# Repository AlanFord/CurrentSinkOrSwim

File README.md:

# CurrentSinkOrSwim
Building a current sink for battery testing in Contextual Electronics.

Here's the project so far:

and

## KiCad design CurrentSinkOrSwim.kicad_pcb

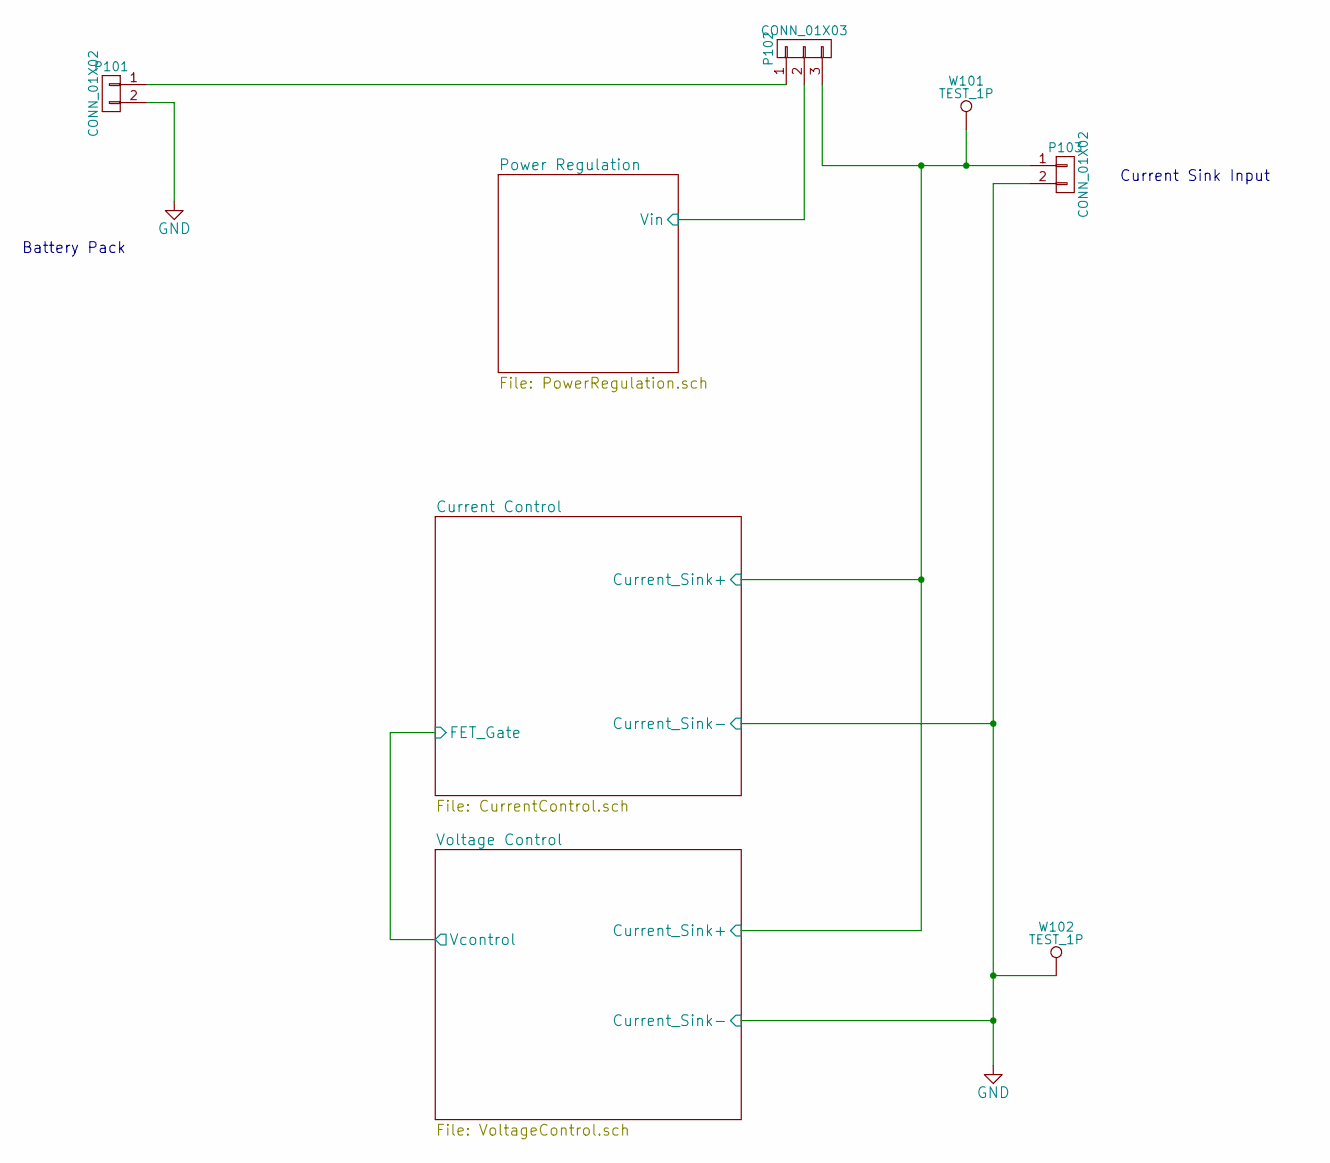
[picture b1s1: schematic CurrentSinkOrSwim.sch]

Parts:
P101, P103: CONN_01X02; Terminal_Block_200_mil; MPN OSTTC022162
P102: CONN_01X03; Pin_Header_Straight_1x03
W101, W102: TEST_1P; Measurement_Point_Round-SMD-Pad_Small

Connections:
/Current Control/Current_Sink+: P102.3, P103.1, W101.1; also elsewhere on the board
/Power Regulation/Vin: P102.2; also elsewhere on the board
GND: P101.2, P103.2, W102.1; also elsewhere on the board
unnamed: P101.1, P102.1

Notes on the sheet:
Battery Pack
Current Sink Input

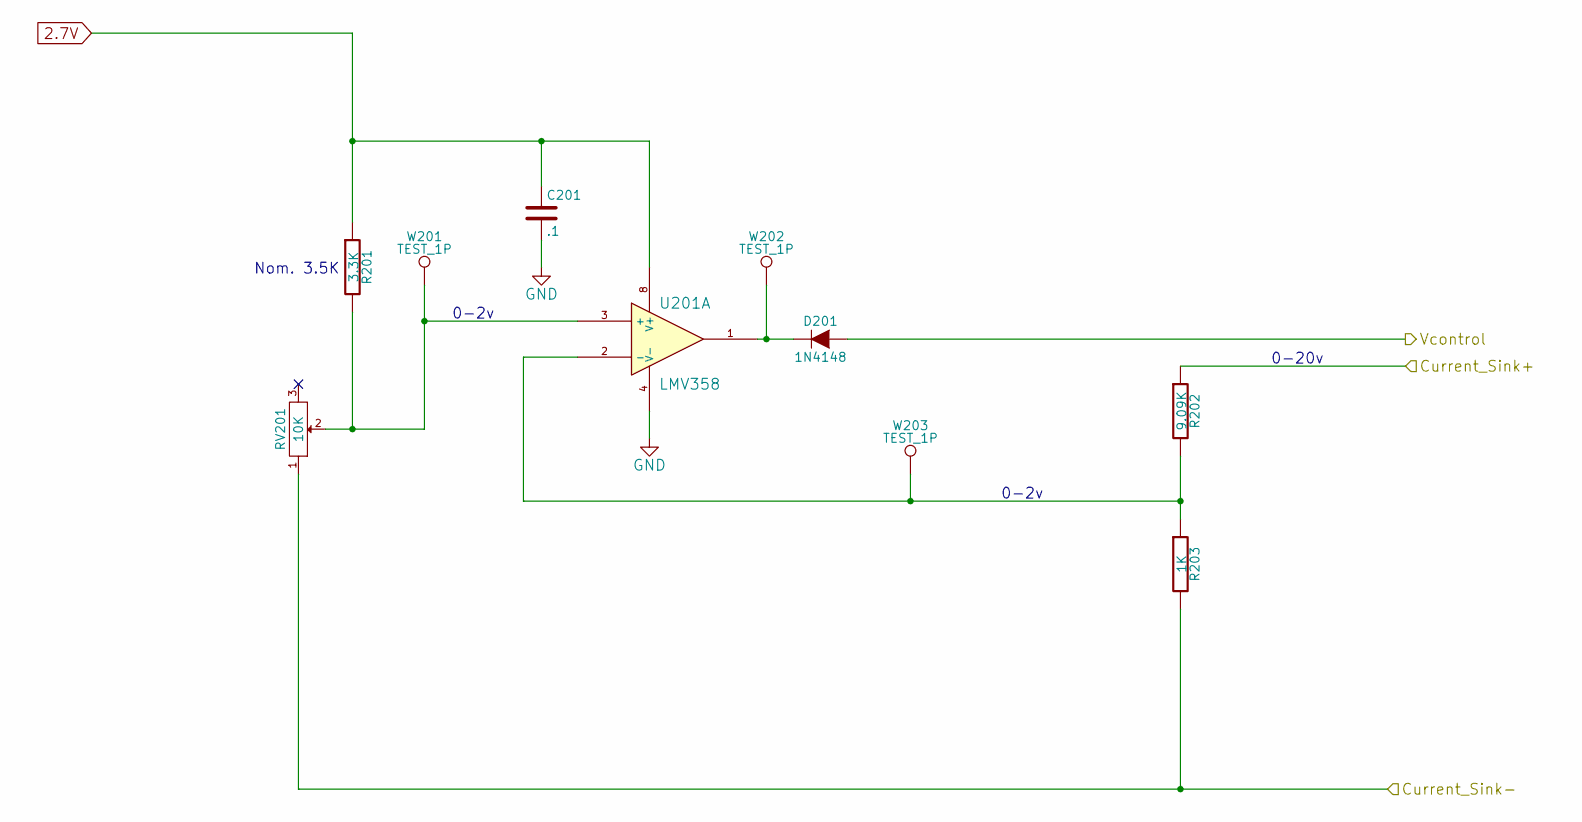
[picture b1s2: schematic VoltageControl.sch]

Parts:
C201: .1; C_0805
D201: 1N4148; SOD-323; MPN 1N4148WS-7-F
R201: 3.3K; R_0805
R202: 9.09K; R_0805
R203: 1K; R_0805
RV201: 10K; P090L-02F25BR10K; MPN P090L-02F25BR10K
U201: LMV358; SOIC-8-N; MPN LMV358IDT
W201, W202, W203: TEST_1P; Measurement_Point_Round-SMD-Pad_Small

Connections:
2.7V: C201.1, R201.1, U201.8 (V+); also elsewhere on the board
/Current Control/Current_Sink+: R202.1; also elsewhere on the board
/Current Control/FET_Gate: D201.2 (A); also elsewhere on the board
GND: C201.2, R203.2, RV201.1, U201.4 (V-); also elsewhere on the board
unnamed: D201.1 (K), U201.1, W202.1
unnamed: R201.2, RV201.2, U201.3 (+), W201.1
unnamed: R202.2, R203.1, U201.2 (-), W203.1

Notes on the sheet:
0-2v
0-20v
Nom. 3.5K

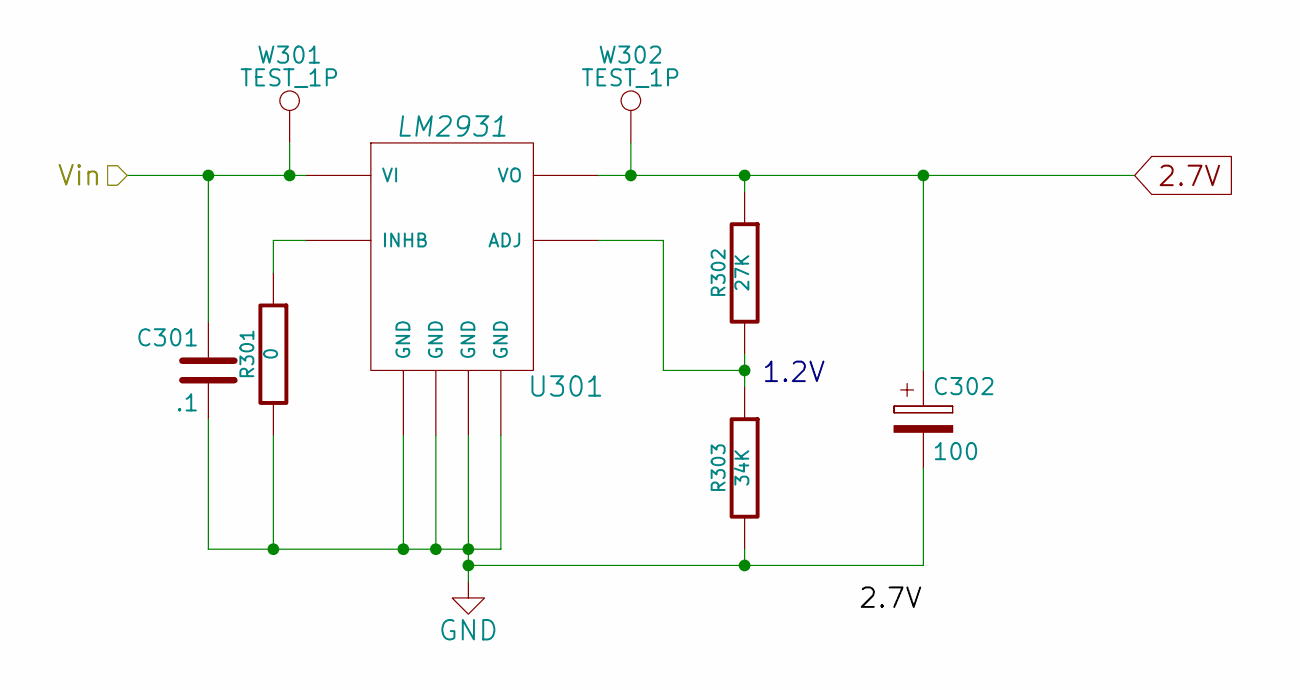
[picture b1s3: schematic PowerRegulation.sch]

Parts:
C301: .1; C_0805
C302: 100; PCE3867CT-ND; MPN PCE3867CT-ND
R301: 0; R_0805; MPN Value
R302: 27K; R_0805; MPN Value
R303: 34K; R_0805
U301: LM2931; SOIC-8-N; MPN LM2931D-R
W301, W302: TEST_1P; Measurement_Point_Round-SMD-Pad_Small

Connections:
2.7V: C302.1, R302.1, U301.1 (VO), W302.1; also elsewhere on the board
/Power Regulation/Vin: C301.1, U301.8 (VI), W301.1; also elsewhere on the board
GND: C301.2, C302.2, R301.2, R303.2, U301.2 (GND), U301.3 (GND), U301.6 (GND), U301.7 (GND); also elsewhere on the board
unnamed: R301.1, U301.5 (INHB)
unnamed: R302.2, R303.1, U301.4 (ADJ)

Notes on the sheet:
1.2V

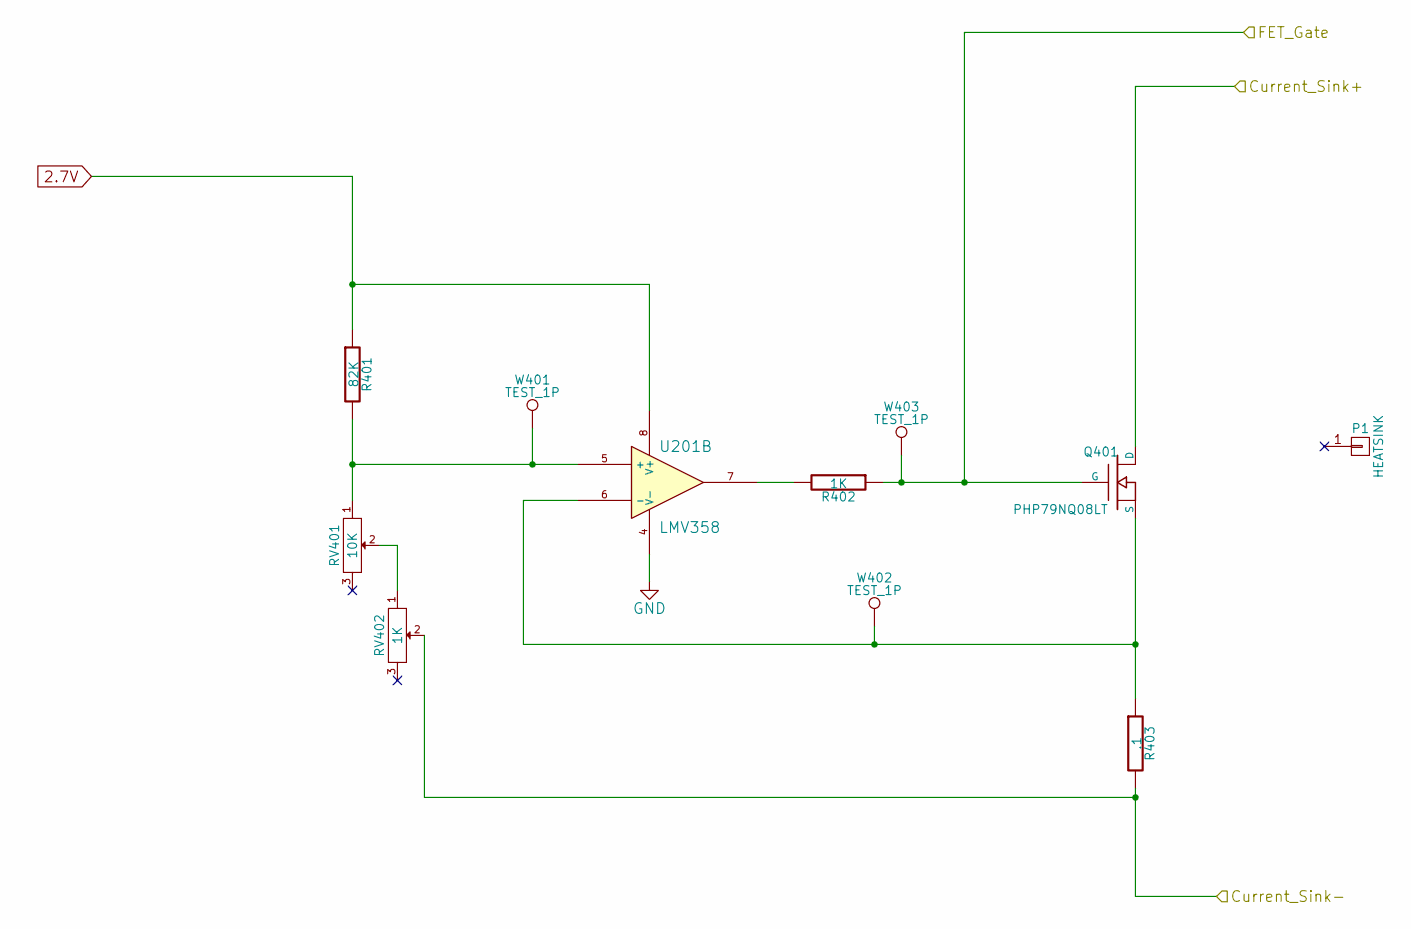
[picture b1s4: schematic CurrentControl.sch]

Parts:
P1: HEATSINK; FA-T220-38E; MPN FA-T220-38E
Q401: PHP79NQ08LT; TO-220_FET-GDS_Vertical; MPN PHP79NQ08LT,127
R401: 82K; R_0805
R402: 1K; R_0805
R403: .1; R_2512; MPN CRA2512-FZ-R100ELF
RV401: 10K; P090L-02F25BR10K; MPN P090L-02F25BR10K
RV402: 1K; MPN P110KV1-1F25BR1K
U201: LMV358; SOIC-8-N
W401, W402, W403: TEST_1P; Measurement_Point_Round-SMD-Pad_Small

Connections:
2.7V: R401.1, U201.8 (V+); also elsewhere on the board
/Current Control/Current_Sink+: Q401.D; also elsewhere on the board
/Current Control/FET_Gate: Q401.G, R402.1, W403.1; also elsewhere on the board
GND: R403.2, RV401.2, RV402.1, RV402.2, U201.4 (V-); also elsewhere on the board
unnamed: Q401.S, R403.1, U201.6 (-), W402.1
unnamed: R401.2, RV401.1, U201.5 (+), W401.1
unnamed: R402.2, U201.7

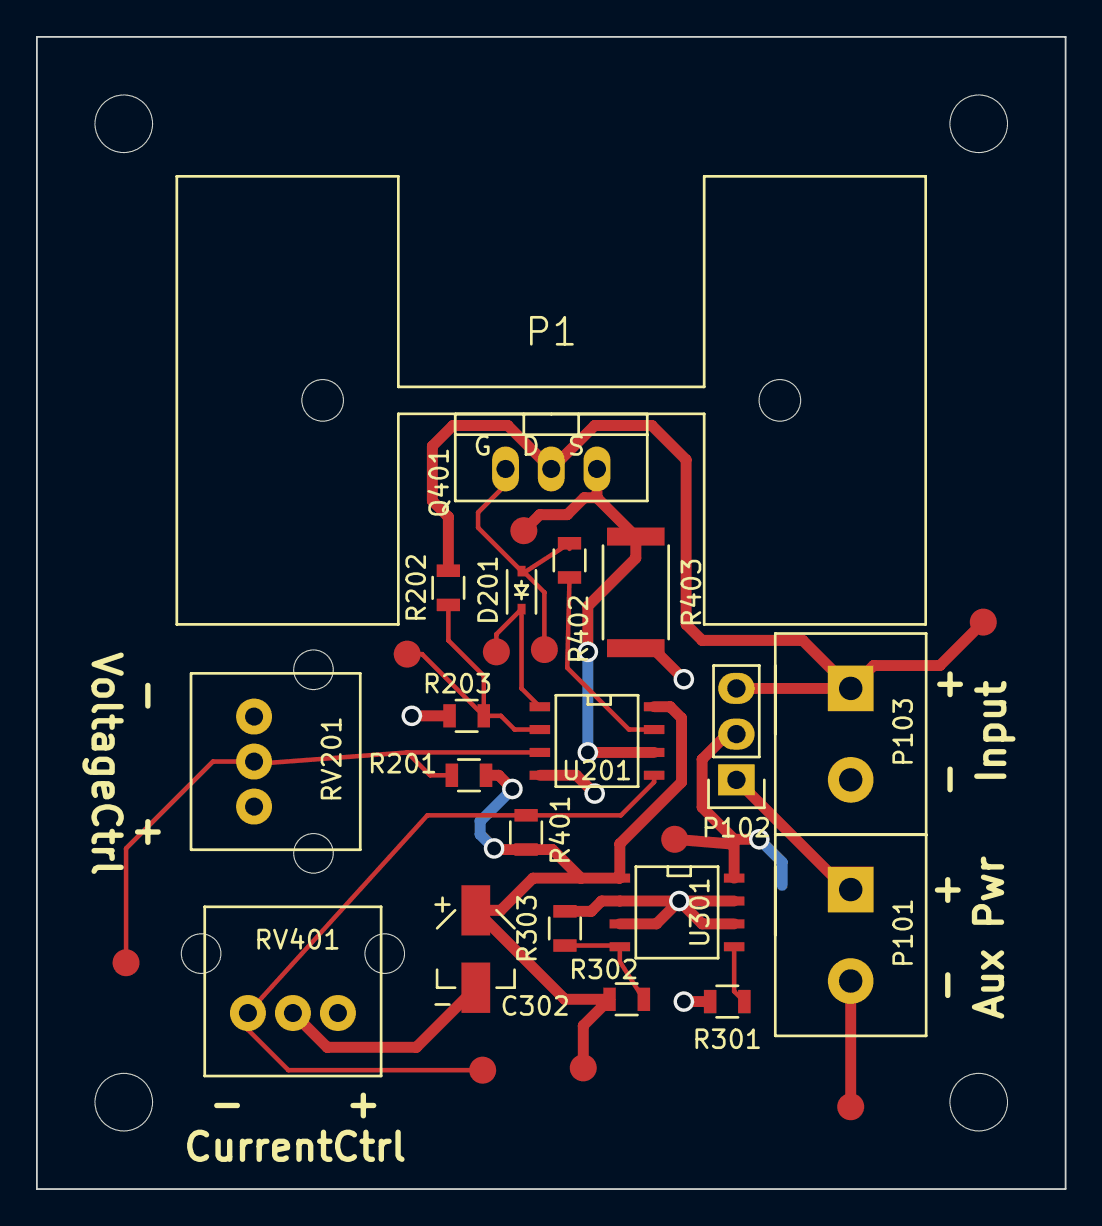
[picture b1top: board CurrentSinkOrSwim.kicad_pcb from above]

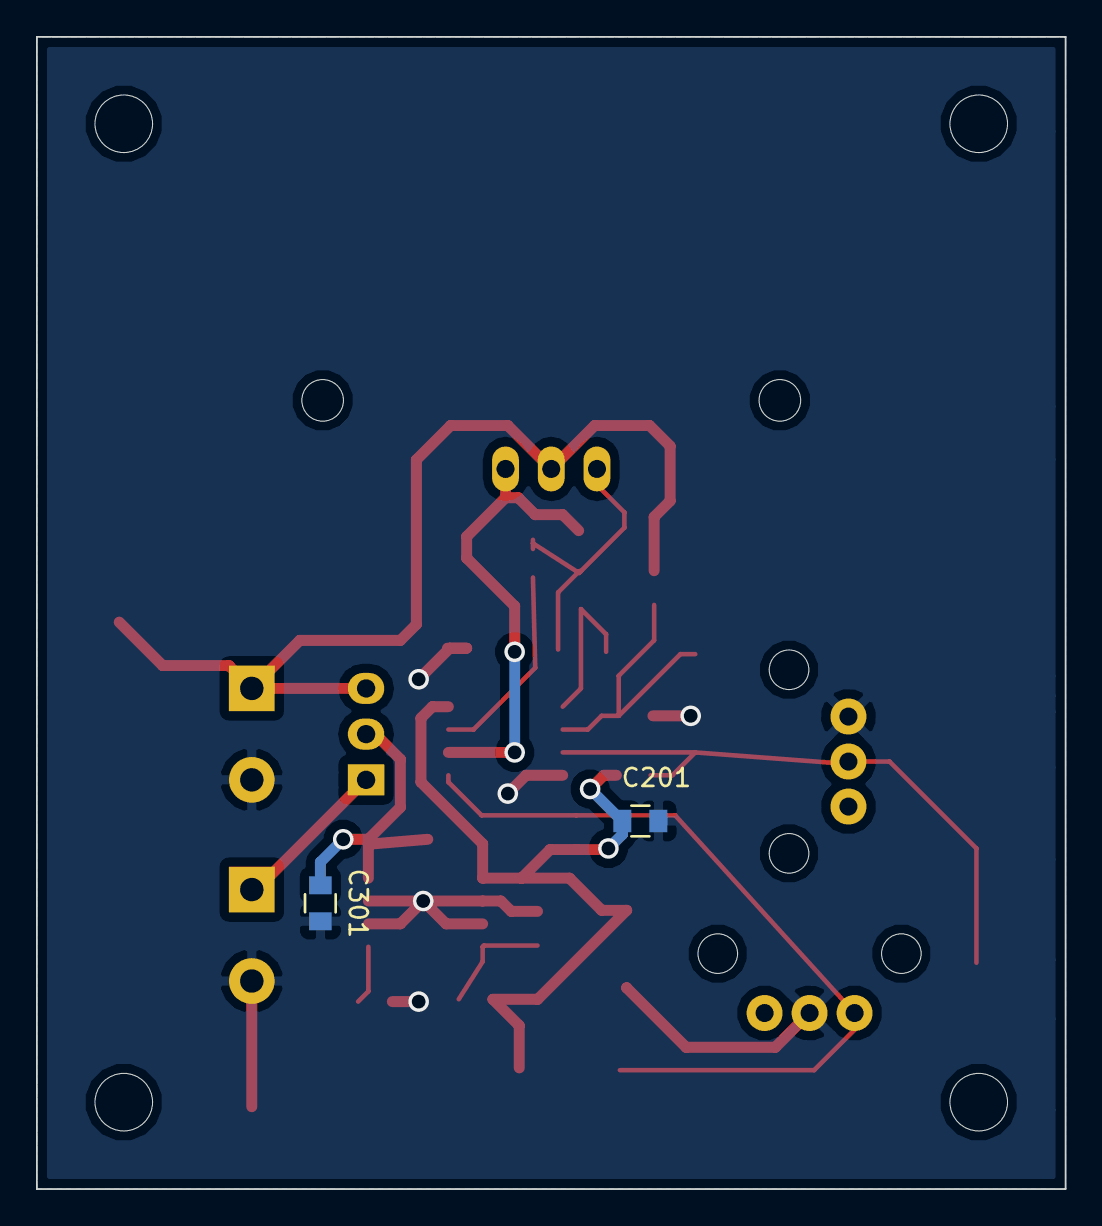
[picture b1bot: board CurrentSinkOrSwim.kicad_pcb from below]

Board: 2 copper layers, 57.1 x 64.0 mm, 32 parts (2 on the bottom side), 14 nets.

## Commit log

2016-08-14 updated project specific pcb library paths to use environment variables
2016-08-14 updated schematic capacitor symbols to use new default library symbols
2016-08-14 deleted orphaned libraries in EEschema, imported updated netlist into PCBNew and checked for errors
2016-08-16 corrected cap on voltage regulator and corrected voltage divider in voltage control
2016-08-22 updated diode to sod-323 package and used new schematic symbol because pin numbers changed
2016-08-22 added datasheet for 100uF cap
2016-08-22 added 100uF pcb footprint and misc comments
2016-08-23 update pot footprints to have circular mounting holes
2016-08-24 initial component placement on the pcb
2016-08-25 added keepout, ground plane, and moved caps to back side
2016-08-27 possible layout with over half of tracks
2016-08-29 added last ground traces, one backside trace, and vias to ground. passes drc.
2016-08-29 fixed edge cut
2016-08-30 updated sikscreen, shifted some components, enlarged ground plane, added mounting holes
2016-09-01 added labels, switched leads on voltage pot so + == clockwise, enlarged ground plane
2016-09-01 added test points to schematic and pcb
2016-09-01 changed sense resistor to 2W, 2512SMD2
2016-09-02 added test point for GND
2016-09-02 added notes for standoffs, jumper, and heat sink mounting
2016-09-03 generated BOM
2016-09-03 updated the gerbers
2016-09-04 revised resistors to match available values, replaced FET (old FET was obsolete/unavail)
2016-09-06 added png images of the board
2016-09-07 reduced size of pcb image to make it more suitable for web page use
2016-09-08 added images to the README
2016-09-08 cleaning up README formatting
2016-09-27 added fine-gain pot to the current control sheet
2016-10-08 Revert "added fine-gain pot to the current control sheet"
    This reverts commit 2c8c25b55c9f8694f13c8f60d96001b4a7e97e34.
    After testing the Rev. 1, didn't need the fine gain potentiometer
2016-11-01 adjusted R303 to get 2.7V, exchanged other parts for availability
2016-11-15 added gerber file for solder stencil
